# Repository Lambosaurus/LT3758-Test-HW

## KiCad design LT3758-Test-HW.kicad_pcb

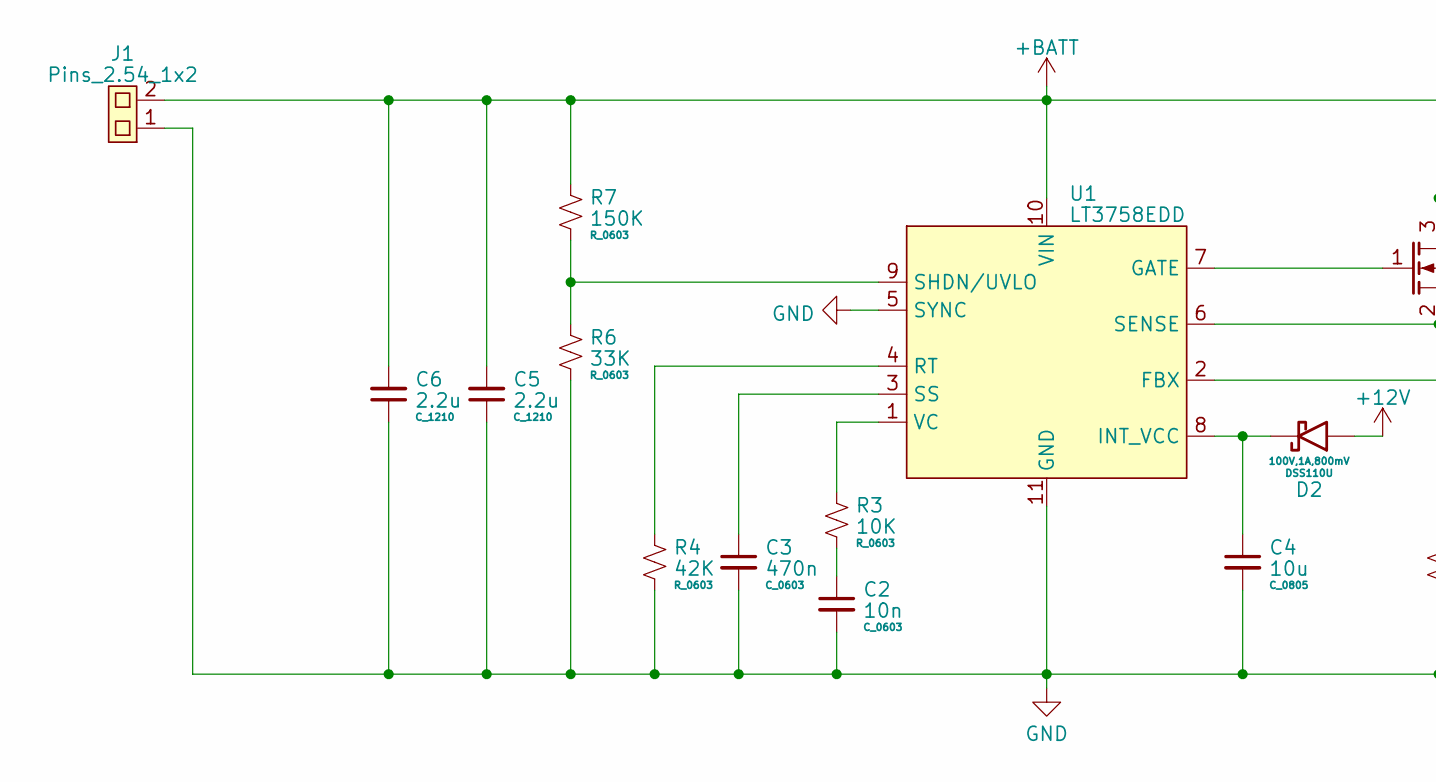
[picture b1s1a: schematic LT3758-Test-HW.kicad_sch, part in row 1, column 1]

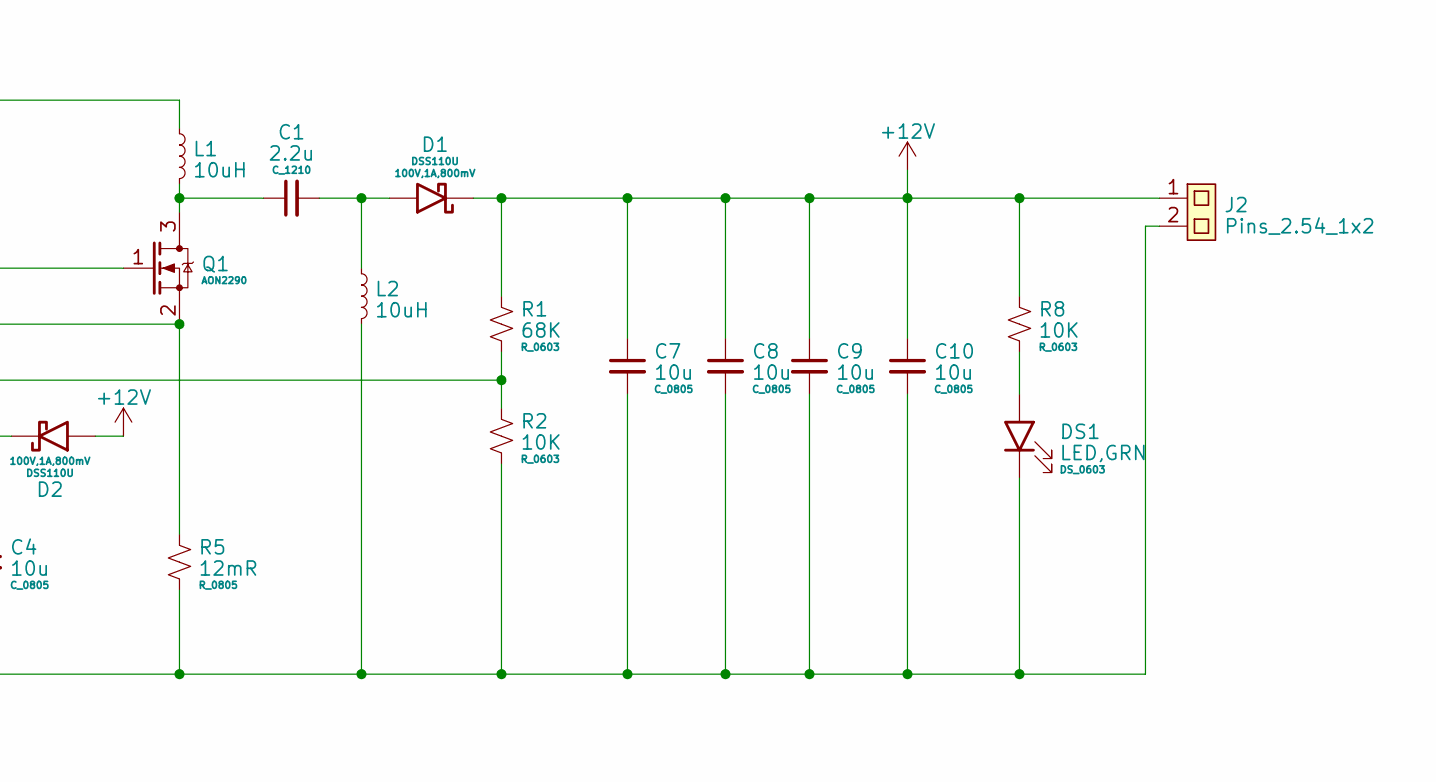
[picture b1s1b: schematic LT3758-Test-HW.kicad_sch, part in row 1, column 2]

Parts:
C1, C5, C6: 2.2u; C_1210
C2: 10n; C_0603
C3: 470n; C_0603
C4, C7, C8, C9, C10: 10u; C_0805
D1, D2: DSS110U; D_SOD_123
DS1: LED,GRN; DS_0603
J1, J2: Pins_2.54_1x2; Pins-2.54-1x2
L1, L2: 10uH; L_1210
Q1: AON2290; U-DFN2020-6
R1: 68K; R_0603
R2, R3, R8: 10K; R_0603
R4: 42K; R_0603
R5: 12mR; R_0805
R6: 33K; R_0603
R7: 150K; R_0603
U1: LT3758EDD; DFN10_05_3x3_EP

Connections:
+12V: C7.1, C8.1, C9.1, C10.1, D1.1, D2.2, J2.1, R1.1, R8.1
+BATT: C5.2, C6.2, J1.2, L1.1, R7.1, U1.10 (VIN)
GND: C2.2, C3.2, C4.2, C5.1, C6.1, C7.2, C8.2, C9.2, C10.2, DS1.1 (K), J1.1, J2.2, L2.2, R2.2, R4.2, R5.2, R6.2, U1.5 (SYNC), U1.11 (GND)
unnamed: C1.2, D1.2, L2.1
unnamed: C2.1, R3.2
unnamed: DS1.2 (A), R8.2
unnamed: C1.1, L1.2, Q1.3 (D)
unnamed: Q1.1 (G), U1.7 (GATE)
unnamed: Q1.2 (S), R5.1, U1.6 (SENSE)
unnamed: R1.2, R2.1, U1.2 (FBX)
unnamed: C4.1, D2.1, U1.8 (INT_VCC)
unnamed: R4.1, U1.4 (RT)
unnamed: R6.1, R7.2, U1.9 (SHDN/UVLO)
unnamed: C3.1, U1.3 (SS)
unnamed: R3.1, U1.1 (VC)

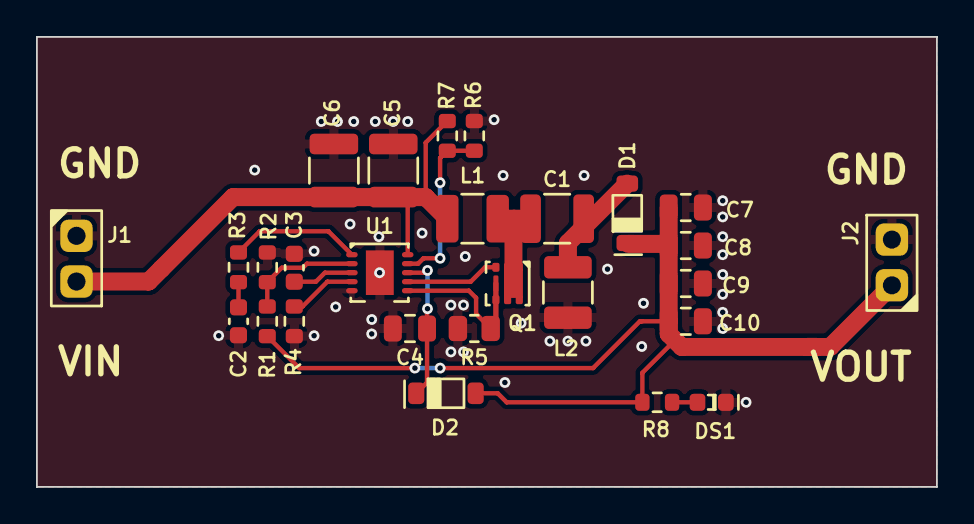
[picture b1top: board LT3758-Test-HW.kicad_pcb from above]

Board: 2 copper layers, 50.0 x 25.0 mm, 27 parts (0 on the bottom side), 15 nets.

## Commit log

2023-07-07 Add text block
